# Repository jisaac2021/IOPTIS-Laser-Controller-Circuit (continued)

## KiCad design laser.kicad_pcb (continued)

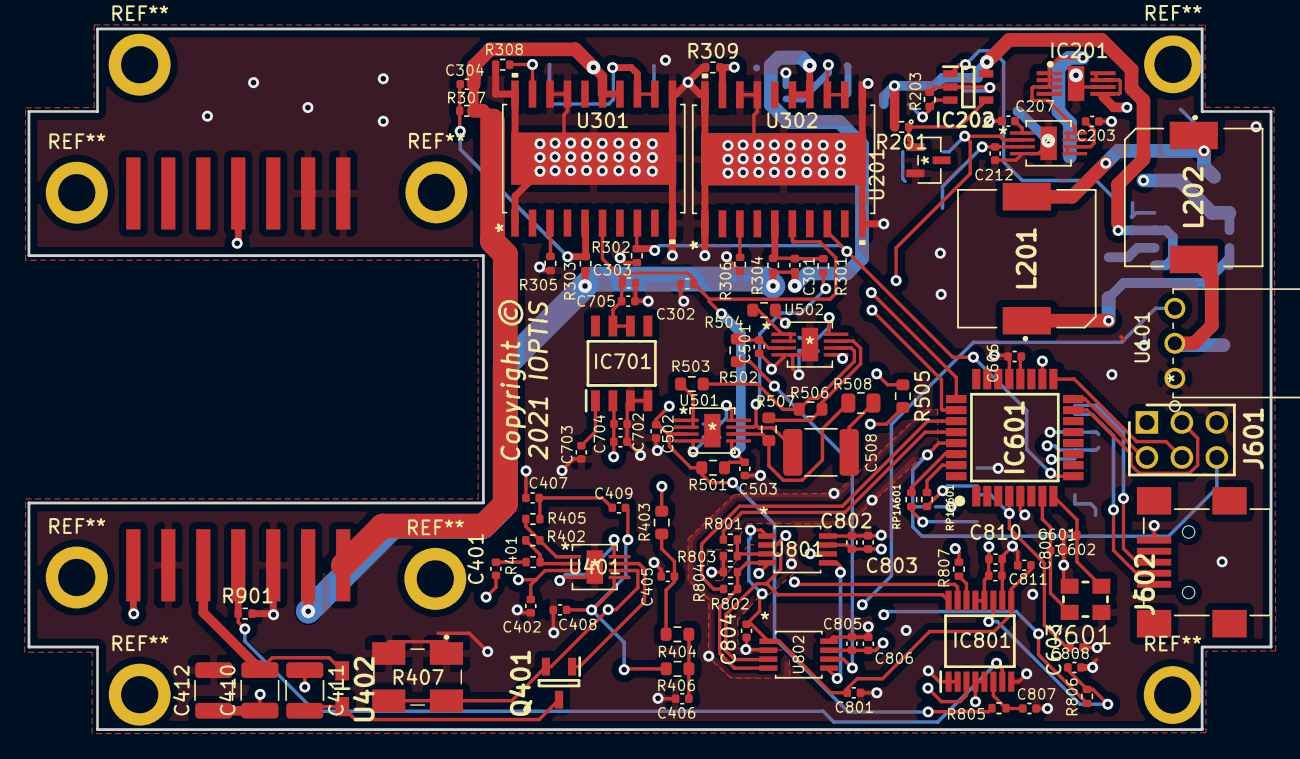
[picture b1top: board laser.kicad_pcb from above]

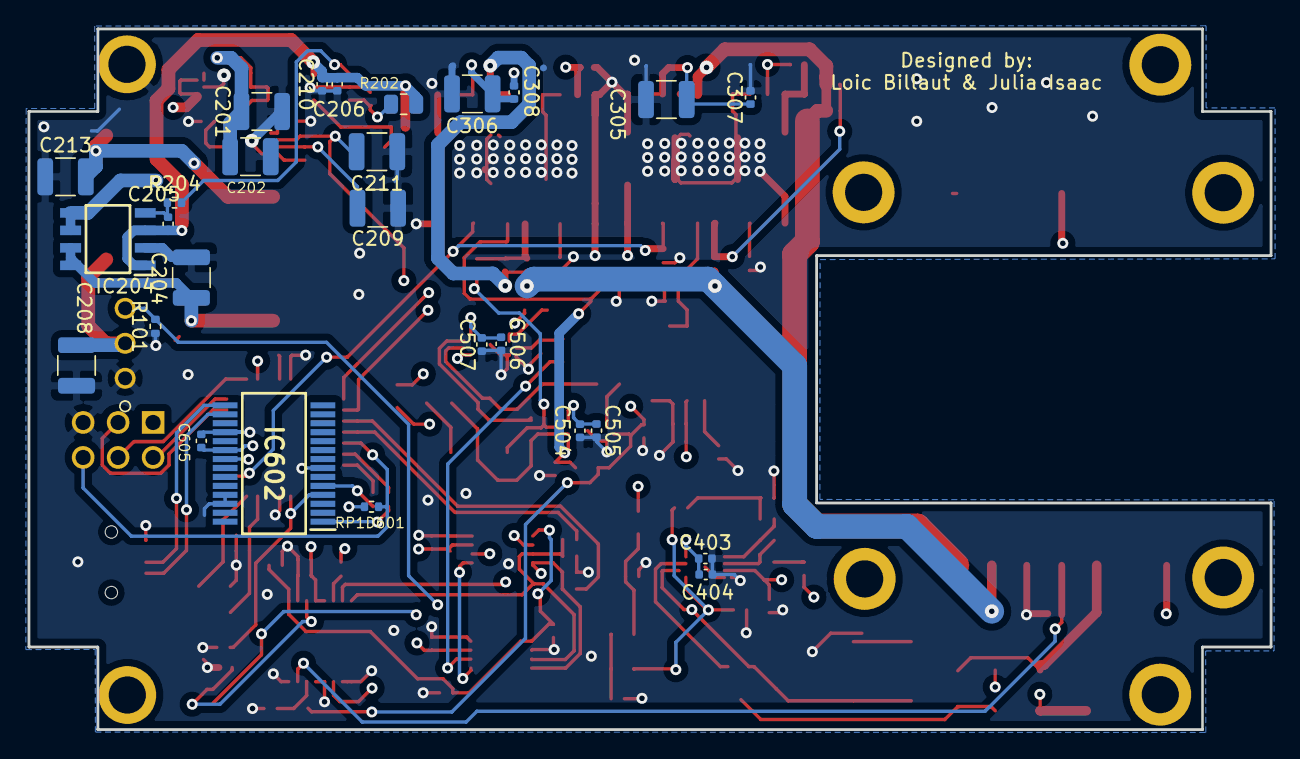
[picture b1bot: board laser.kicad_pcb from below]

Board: 4 copper layers, 90.2 x 50.9 mm, 126 parts (27 on the bottom side), 71 nets.

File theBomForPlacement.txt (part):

"Source:"	"C:\Users\lsbil\IOPTIS-Laser-Controller-Circuit\laser.sch"
"Date:"	"7/23/2021 2:19:18 PM"
"Tool:"	"Eeschema (5.1.10)-1"
"Component Count:"	"124"
"Ref"	"Value"	"Part"	"Footprint"	"Description"	"Vendor"
"B1"	"butterfly"	"New_Library_for_first_symbol:butterfly"	"footprint libraries:Butterfly"	""	""
"C201"	"100u"	"Device:C"	"Capacitor_SMD:C_1210_3225Metric"	"Unpolarized capacitor"	""
"C202"	"100u"	"Device:C"	"Capacitor_SMD:C_1210_3225Metric"	"Unpolarized capacitor"	""
"C203"	"1u"	"Device:C"	"Capacitor_SMD:C_0402_1005Metric"	"Unpolarized capacitor"	""
"C204"	"100u"	"Device:C"	"Capacitor_SMD:C_1210_3225Metric"	"Unpolarized capacitor"	""
"C205"	"2.2u"	"Device:C"	"Capacitor_SMD:C_0402_1005Metric"	"Unpolarized capacitor"	""
"C206"	"1u"	"Device:C"	"Capacitor_SMD:C_0402_1005Metric"	"Unpolarized capacitor"	""
"C207"	"10u"	"Device:C"	"Capacitor_SMD:C_0402_1005Metric"	"Unpolarized capacitor"	""
"C208"	"100u"	"Device:C"	"Capacitor_SMD:C_1210_3225Metric"	"Unpolarized capacitor"	""
"C209"	"100u"	"Device:C"	"Capacitor_SMD:C_1210_3225Metric"	"Unpolarized capacitor"	""
"C210"	"0.1u"	"Device:C"	"Capacitor_SMD:C_0402_1005Metric"	"Unpolarized capacitor"	""
"C211"	"100u"	"Device:C"	"Capacitor_SMD:C_1210_3225Metric"	"Unpolarized capacitor"	""
"C212"	"1u"	"Device:C"	"Capacitor_SMD:C_0402_1005Metric"	"Unpolarized capacitor"	""
"C301"	"10u"	"Device:C"	"Capacitor_SMD:C_0402_1005Metric"	"Unpolarized capacitor"	""
"C302"	"0.1u"	"Device:C"	"Capacitor_SMD:C_0402_1005Metric"	"Unpolarized capacitor"	""
"C303"	"0.1u"	"Device:C"	"Capacitor_SMD:C_0402_1005Metric"	"Unpolarized capacitor"	""
"C304"	"10u"	"Device:C"	"Capacitor_SMD:C_0402_1005Metric"	"Unpolarized capacitor"	""
"C305"	"100u"	"Device:C"	"Capacitor_SMD:C_1210_3225Metric"	"Unpolarized capacitor"	""
"C306"	"100u"	"Device:C"	"Capacitor_SMD:C_1210_3225Metric"	"Unpolarized capacitor"	""
"C307"	"0.1u"	"Device:C"	"Capacitor_SMD:C_0402_1005Metric"	"Unpolarized capacitor"	""
"C308"	"0.1u"	"Device:C"	"Capacitor_SMD:C_0402_1005Metric"	"Unpolarized capacitor"	""
"C401"	"1u"	"Device:C"	"Capacitor_SMD:C_0402_1005Metric"	"Unpolarized capacitor"	""
"C402"	"0.1u"	"Device:C"	"Capacitor_SMD:C_0402_1005Metric"	"Unpolarized capacitor"	""
"C403"	"1u"	"Device:C"	"Capacitor_SMD:C_0402_1005Metric"	"Unpolarized capacitor"	""
"C404"	"0.1u"	"Device:C"	"Capacitor_SMD:C_0402_1005Metric"	"Unpolarized capacitor"	""
"C405"	"10u"	"Device:C"	"Capacitor_SMD:C_0402_1005Metric"	"Unpolarized capacitor"	""
"C406"	"10u"	"Device:C"	"Capacitor_SMD:C_0402_1005Metric"	"Unpolarized capacitor"	""
"C407"	"0.1u"	"Device:C"	"Capacitor_SMD:C_0402_1005Metric"	"Unpolarized capacitor"	""
"C408"	"0.01u"	"Device:C"	"Capacitor_SMD:C_0402_1005Metric"	"Unpolarized capacitor"	""
"C409"	"1u"	"Device:C"	"Capacitor_SMD:C_0402_1005Metric"	"Unpolarized capacitor"	""
"C410"	"100u"	"Device:C"	"Capacitor_SMD:C_1210_3225Metric"	"Unpolarized capacitor"	""
"C411"	"100u"	"Device:C"	"Capacitor_SMD:C_1210_3225Metric"	"Unpolarized capacitor"	""
"C412"	"100u"	"Device:C"	"Capacitor_SMD:C_1210_3225Metric"	"Unpolarized capacitor"	""
"C501"	"2.2u"	"Device:C"	"Capacitor_SMD:C_0402_1005Metric"	"Unpolarized capacitor"	""
"C502"	"2.2u"	"Device:C"	"Capacitor_SMD:C_0402_1005Metric"	"Unpolarized capacitor"	""
"C503"	"0.1u"	"Device:C"	"Capacitor_SMD:C_0402_1005Metric"	"Unpolarized capacitor"	""
"C504"	"0.1u"	"Device:C"	"Capacitor_SMD:C_0402_1005Metric"	"Unpolarized capacitor"	""
"C505"	"1u"	"Device:C"	"Capacitor_SMD:C_0402_1005Metric"	"Unpolarized capacitor"	""
"C506"	"0.1u"	"Device:C"	"Capacitor_SMD:C_0402_1005Metric"	"Unpolarized capacitor"	""
"C507"	"1u"	"Device:C"	"Capacitor_SMD:C_0402_1005Metric"	"Unpolarized capacitor"	""
"C508"	"6.8u"	"Device:C"	"Capacitor_SMD:C_1812_4532Metric"	"Unpolarized capacitor"	""
"C601"	"C"	"Device:C"	"Capacitor_SMD:C_0402_1005Metric"	"Unpolarized capacitor"	""
"C602"	"C"	"Device:C"	"Capacitor_SMD:C_0402_1005Metric"	"Unpolarized capacitor"	""
"C603"	"1uf"	"Device:C"	"Capacitor_SMD:C_0402_1005Metric"	"Unpolarized capacitor"	""
"C605"	"1uf"	"Device:C"	"Capacitor_SMD:C_0402_1005Metric"	"Unpolarized capacitor"	""
"C606"	"100nF"	"Device:C"	"Capacitor_SMD:C_0402_1005Metric"	"Unpolarized capacitor"	""
"C702"	"0.1u"	"Device:C"	"Capacitor_SMD:C_0402_1005Metric"	"Unpolarized capacitor"	""
"C703"	"0.1u"	"Device:C"	"Capacitor_SMD:C_0402_1005Metric"	"Unpolarized capacitor"	""
"C704"	"1u"	"Device:C"	"Capacitor_SMD:C_0402_1005Metric"	"Unpolarized capacitor"	""
"C705"	"0.1u"	"Device:C"	"Capacitor_SMD:C_0402_1005Metric"	"Unpolarized capacitor"	""
"C801"	"0.1u"	"Device:C"	"Capacitor_SMD:C_0402_1005Metric"	"Unpolarized capacitor"	""
"C802"	"1u"	"Device:C"	"Capacitor_SMD:C_0402_1005Metric"	"Unpolarized capacitor"	""
"C803"	"0.1u"	"Device:C"	"Capacitor_SMD:C_0402_1005Metric"	"Unpolarized capacitor"	""
"C804"	"0.1u"	"Device:C"	"Capacitor_SMD:C_0402_1005Metric"	"Unpolarized capacitor"	""
"C805"	"1u"	"Device:C"	"Capacitor_SMD:C_0402_1005Metric"	"Unpolarized capacitor"	""
"C806"	"0.1u"	"Device:C"	"Capacitor_SMD:C_0402_1005Metric"	"Unpolarized capacitor"	""
"C807"	"1u"	"Device:C"	"Capacitor_SMD:C_0402_1005Metric"	"Unpolarized capacitor"	""
"C808"	"1u"	"Device:C"	"Capacitor_SMD:C_0402_1005Metric"	"Unpolarized capacitor"	""
"C809"	"0.1u"	"Device:C"	"Capacitor_SMD:C_0402_1005Metric"	"Unpolarized capacitor"	""
"C810"	"1u"	"Device:C"	"Capacitor_SMD:C_0402_1005Metric"	"Unpolarized capacitor"	""
"C811"	"0.1u"	"Device:C"	"Capacitor_SMD:C_0402_1005Metric"	"Unpolarized capacitor"	""
"IC201"	"ADM7172ACPZ-4.2-R7"	"ADM7172ACPZ-4.2-R7:ADM7172ACPZ-4.2-R7"	"footprint libraries:ADM7172ACPZ-4.2-R7"	""	""
"IC202"	"LT1716CS5#TRPBF"	"LT1716CS5#TRPBF:LT1716CS5#TRPBF"	"footprint libraries:LT1716CS5#TRPBF"	""	""
"IC203"	"ADM7154ARDZ-3.3-R7"	"ADM7154ARDZ-3.3-R7:ADM7154ARDZ-3.3-R7"	"footprint libraries:ADA4528-2ACPZ-RL"	""	""
"IC204"	"IRF9358PBF"	"IRF9358PBF:IRF9358PBF"	"footprint libraries:IRF9358PBF"	""	""
"IC601"	"ATMEGA328PB-AN"	"ATMEGA328PB-AN:ATMEGA328PB-AN"	"footprint libraries:QFP80P900X900X120-32N"	""	""
"IC602"	"FT232RL-TUBE"	"laser-rescue:FT232RL-TUBE-FT232RL-TUBE-laser-rescue-laser-rescue-laser-rescue"	"footprint libraries:FT232RL-TUBE"	""	""
"IC701"	"MAX6126AASA25+"	"MAX6126AASA25+:MAX6126AASA25+"	"footprint libraries:MAX6126-25+"	""	""
"IC801"	"ADS122C04IPWR"	"ADS122C04IPWR:ADS122C04IPWR"	"footprint libraries:ADS122C04IPWR"	""	""
"J601"	"M20-9980345"	"M20-9980345:M20-9980345"	"footprint libraries:M20-9980345"	""	""
"J602"	"USB_Connector"	"New_Library_for_first_symbol:USB_Connector"	"footprint libraries:UX60MB5ST"	""	""
"L201"	"100u"	"7447714101:7447714101"	"footprint libraries:7447714220"	""	""
"Q401"	"RSR030N06TL"	"RSR030N06TL:RSR030N06TL"	"footprint libraries:RSR030N06TL"	""	""
"R101"	"3.3k"	"Device:R"	"Resistor_SMD:R_0402_1005Metric"	"Resistor"	""
"R201"	"10k"	"Device:R"	"Resistor_SMD:R_0402_1005Metric"	"Resistor"	""
"R202"	"14k"	"Device:R"	"Resistor_SMD:R_0805_2012Metric"	"Resistor"	""
"R203"	"12k"	"Device:R"	"Resistor_SMD:R_0402_1005Metric"	"Resistor"	""
"R204"	"47k"	"Device:R"	"Resistor_SMD:R_0402_1005Metric"	"Resistor"	""
"R301"	"470"	"Device:R"	"Resistor_SMD:R_0402_1005Metric"	"Resistor"	""
"R302"	"10k"	"Device:R"	"Resistor_SMD:R_0402_1005Metric"	"Resistor"	""
"R303"	"470"	"Device:R"	"Resistor_SMD:R_0402_1005Metric"	"Resistor"	""
"R304"	"470"	"Device:R"	"Resistor_SMD:R_0402_1005Metric"	"Resistor"	""
"R305"	"10k"	"Device:R"	"Resistor_SMD:R_0402_1005Metric"	"Resistor"	""
"R306"	"10k"	"Device:R"	"Resistor_SMD:R_0402_1005Metric"	"Resistor"	""
"R307"	"470"	"Device:R"	"Resistor_SMD:R_0402_1005Metric"	"Resistor"	""
"R308"	"470"	"Device:R"	"Resistor_SMD:R_0402_1005Metric"	"Resistor"	""
"R309"	"470"	"Device:R"	"Resistor_SMD:R_0402_1005Metric"	"Resistor"	""
"R401"	"1k"	"Device:R"	"Resistor_SMD:R_0402_1005Metric"	"Resistor"	""
"R402"	"1k"	"Device:R"	"Resistor_SMD:R_0402_1005Metric"	"Resistor"	""
"R403"	"10k"	"Device:R"	"Resistor_SMD:R_0603_1608Metric"	"Resistor"	""
"R404"	"10k"	"Device:R"	"Resistor_SMD:R_0603_1608Metric"	"Resistor"	""
"R405"	"100"	"Device:R"	"Resistor_SMD:R_0402_1005Metric"	"Resistor"	""
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
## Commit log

2021-06-09 Setup subsheets
2021-06-09 second commit
2021-06-09 third commit
2021-06-09 add ADM7172ACPZ-4.2-R7 library
2021-06-09 add ADM7154ARDZ-3.3-R7 library
2021-06-09 fourth commit
2021-06-09 name change
2021-06-09 fifth
2021-06-09 added mosfet
2021-06-09 add LM4040
2021-06-09 catching up
2021-06-09 remove laser rescue
2021-06-09 testing the library
2021-06-09 recover symbols
2021-06-09 something
2021-06-09 getting libraries to work
2021-06-10 finished the thermal control schematic?
2021-06-10 forgot to save before doing the last one LOL
2021-06-11 add LT1716
2021-06-12 finished thermal control on friday
2021-06-14 put capacitors b/w gnd and power
2021-06-14 added labels for loose ends
2021-06-14 working on second circuit
2021-06-14 finish power supply schematic
2021-06-14 reload libs
2021-06-14 push final edits so i can clone
2021-06-14 add OPA
2021-06-14 added newBoardPowerSupply to the folder
2021-06-14 grounded GND pin on 4.2V regulator
2021-06-14 unconnect R3 and R5 to ground
2021-06-14 powerOpAmpBoard ready for QA
2021-06-15 added capacitors on power op amp schematic
2021-06-15 finish current control schematic
2021-06-15 add RSR030
2021-06-15 merge
2021-06-15 add tiny sch
2021-06-15 added HUUGE hierarchical sheet
2021-06-15 added HUUGE and max library
2021-06-15 finish tiny sch
2021-06-15 added new ferrite bead symbol & footprint to library
2021-06-15 add MAX and ADS
2021-06-15 started on nano sheet
2021-06-15 QA'd, added 2 caps, noted where laser should be
2021-06-15 added ferrite bead symbol to library
2021-06-15 halfway
2021-06-15 update cache
2021-06-15 added new sym into library using correct folder
2021-06-15 finish big sch + add appropriate labels
2021-06-15 added 4.2V port from pwr supply to pwr op amps sheet
2021-06-15 add resistors to both chips
2021-06-15 cache
2021-06-15 finish QA - Julia
2021-06-15 committing everything
2021-06-15 deleted bad usb port thing
2021-06-15 add FT
2021-06-15 committing before pulling
2021-06-15 start wiring FT
2021-06-15 added second usb library
2021-06-15 space labels
2021-06-15 committed changes before pull
2021-06-15 reload FT
2021-06-15 added usb connector
2021-06-16 Revert "nano"
    This reverts commit 4d6fd5897fac472e79c13fb1ab6d35398c5daa14, reversing
    changes made to 8aae38f125b68b2cd7fe44fff7f0dd0a54c9a2a8.
2021-06-16 flipped connector and grounded
2021-06-16 removed rescue file from library
2021-06-16 just deleted reset on nano chip
2021-06-16 finish USB IC1
2021-06-16 add M20 + finish
2021-06-16 annotate all sheets
2021-06-16 reset annotations for tiny, huuge, nano; moved some refs in nano
2021-06-16 finalized nano (references, one more resistor...)
2021-06-16 added new kicad_mod libs to footprint libraries
2021-06-16 add footprints
2021-06-16 added opa thing
2021-06-16 add footprints julia
2021-06-16 added irf footprint
2021-06-16 add footprints 2 julia
2021-06-16 assigned irf footprint
2021-06-16 added vishay dude & capacitor & resistor footprints
2021-06-16 changed all 'odd' resistors in thermal control footprints
2021-06-16 fix spacing
2021-06-16 added osciallator libs
2021-06-16 replace crystal
2021-06-16 add coil
2021-06-17 replaced thermistor w/ butterfly
2021-06-17 changes on nano and laser
2021-06-17 added 3 pin header
2021-06-17 mod signal
2021-06-17 revise AtoD
2021-06-17 add 5V label
2021-06-17 added 5v power source 'ports'
2021-06-17 connect 5V label from nano on main
2021-06-17 ground
2021-06-17 added some more ports
2021-06-17 add mod symbol
2021-06-17 adding 'ports'
2021-06-17 add final 5v connector
2021-06-17 pushing other ports
2021-06-17 added other ports
2021-06-17 added more ports
2021-06-17 pushing all changes and ports
2021-06-17 keep on adding global labels
2021-06-17 name changes
2021-06-17 name change on main for sheets
2021-06-17 adding labels
2021-06-17 replace heirarchal w/ global
2021-06-17 commit changes
2021-06-17 redo annotations
2021-06-17 remove excess wires
2021-06-17 add thermal control output
2021-06-17 did current control
2021-06-17 FINISHED
2021-06-17 adding some more labels
2021-06-18 FINISHED nano, power op amps
2021-06-18 made butterfly a global label, connected SDA & SCL
2021-06-18 just added new sheet for butterfly
2021-06-18 add butterfly custom sym
2021-06-18 TEC on butterfly
2021-06-18 finish monitor on butterfly
2021-06-18 FINISH Butterfly for QA
2021-06-18 finished butterfly footprint
2021-06-18 assigned butterfly footprint
2021-06-18 add pin numbers to ferrite bead
2021-06-18 fixed footprint for ux60 and 7828
2021-06-18 started pcb layout, confused about pours
2021-06-18 added laser.net file
2021-06-18 SOLVED: GND and 4.2V
2021-06-18 updated the netlist on pcb editor
2021-06-18 changed second 4.2V to GND short in pwropAmps
2021-06-19 final push for any last changes 6/18
2021-06-21 GND works
2021-06-21 trying to figure out how to connect gnd to plane
2021-06-21 connect ground
2021-06-21 finished initial layout
2021-06-21 laid out reference and current resistors/caps
2021-06-21 finish placing power supply
2021-06-21 generated new netlist with monitor and ground unshorted
2021-06-21 c305 fixing
2021-06-21 reload C305 and C306
2021-06-21 finished positioning opamps
2021-06-21 finish placing thermalcontrol
2021-06-21 component placement completed
2021-06-22 final edits since Monday
2021-06-22 added one reisistor to monitor pin
2021-06-22 connect all opa pads to ground
2021-06-22 grounded epad in therm control
2021-06-22 grounded all other epads
2021-06-22 make traces 0.5 mm
2021-06-22 grounded epad on pcb
2021-06-22 added 5V
2021-06-22 update power op amps sch
2021-06-22 added 3.3
2021-06-22 added half a trace for 5v ext
2021-06-22 added grounds, finished 5v ext trace
2021-06-22 update netlist from current QA
2021-06-22 pb footprint
2021-06-23 added more traces, plus a few grounds. vias on epads as well
2021-06-23 connect all grounds? maybe?
2021-06-23 added one more epad to gnd on current control
2021-06-23 almost done with traces for power supply
2021-06-23 All grounds connected, power supply done working on cpu
2021-06-23 update sizes on power supply
2021-06-24 finished power op amps as well
2021-06-24 added other traces at home
2021-06-25 finished everything. notes: thick traces, gnd pours, keep outs/pwr plane, DRC Errors
2021-06-25 no more errors in DRC except for th pads
2021-06-25 weird airwires
2021-06-25 COMPLETE for QA
2021-06-25 added keepout under cpu
2021-06-26 almost done w/ silkscreen
2021-06-26 added top copper pour
2021-06-26 finish silkscreen:
2021-07-13 enlarge one pad
2021-07-14 QA 7/13 added new usb, made pads smaller, qa'd everything except current control, arduino and thermal control
2021-07-14 Finished.
2021-07-15 final gerber zip added. name is 'ioptis-laser-gerbers-zip'
2021-07-23 24pf and got rid of f's
2021-07-26 changed silkscreen dot for power op amps
2021-08-04 switched butterfly direction, moved capacitors and inductor, flipped 5v external chip to back
2021-08-05 NEXT PROTO READY 8/5
2021-08-06 plotting gerbers for new gen now
2021-08-18 new-gen-ioptis-pcb added
2021-08-18 restored laer.Kicad
2021-09-14 eliminate gnd loops, unground mounting holes except one, move capacitors interfering with case, move LC filters to beginning of 5V, got rid of 5V plane
2021-09-15 added ground plane, more vias to minimize ground loops
